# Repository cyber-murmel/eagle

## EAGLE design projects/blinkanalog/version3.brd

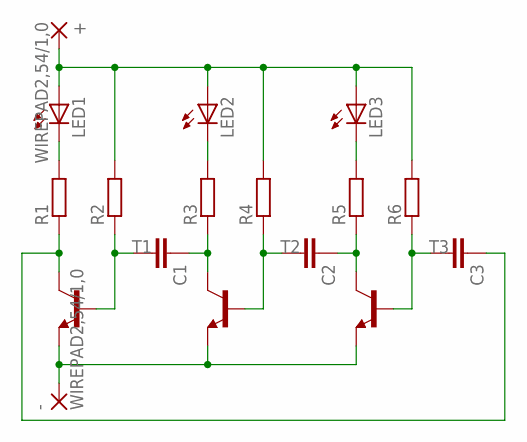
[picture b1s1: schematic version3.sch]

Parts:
+: WIREPAD2,54/1,0; 2,54/1,0
-: WIREPAD2,54/1,0; 2,54/1,0
C1, C2, C3: C-EUC0603; C0603
LED1, LED2, LED3: LEDSML0603; SML0603
R1, R2, R3, R4, R5, R6: R-EU_R0603; R0603
T1, T2, T3: MMBT2222ALT1-NPN-SOT23-BEC; SOT23-BEC

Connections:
unnamed: LED1.C, R1.2
unnamed: C3.1, R1.1, T1.C
unnamed: C1.1, R3.1, T2.C
unnamed: LED2.C, R3.2
unnamed: C2.2, R4.1, T2.B
unnamed: C1.2, R2.1, T1.B
unnamed: +.1, LED1.A, LED2.A, LED3.A, R2.2, R4.2, R6.2
unnamed: C2.1, R5.1, T3.C
unnamed: -.1, T1.E, T2.E, T3.E
unnamed: LED3.C, R5.2
unnamed: C3.2, R6.1, T3.B

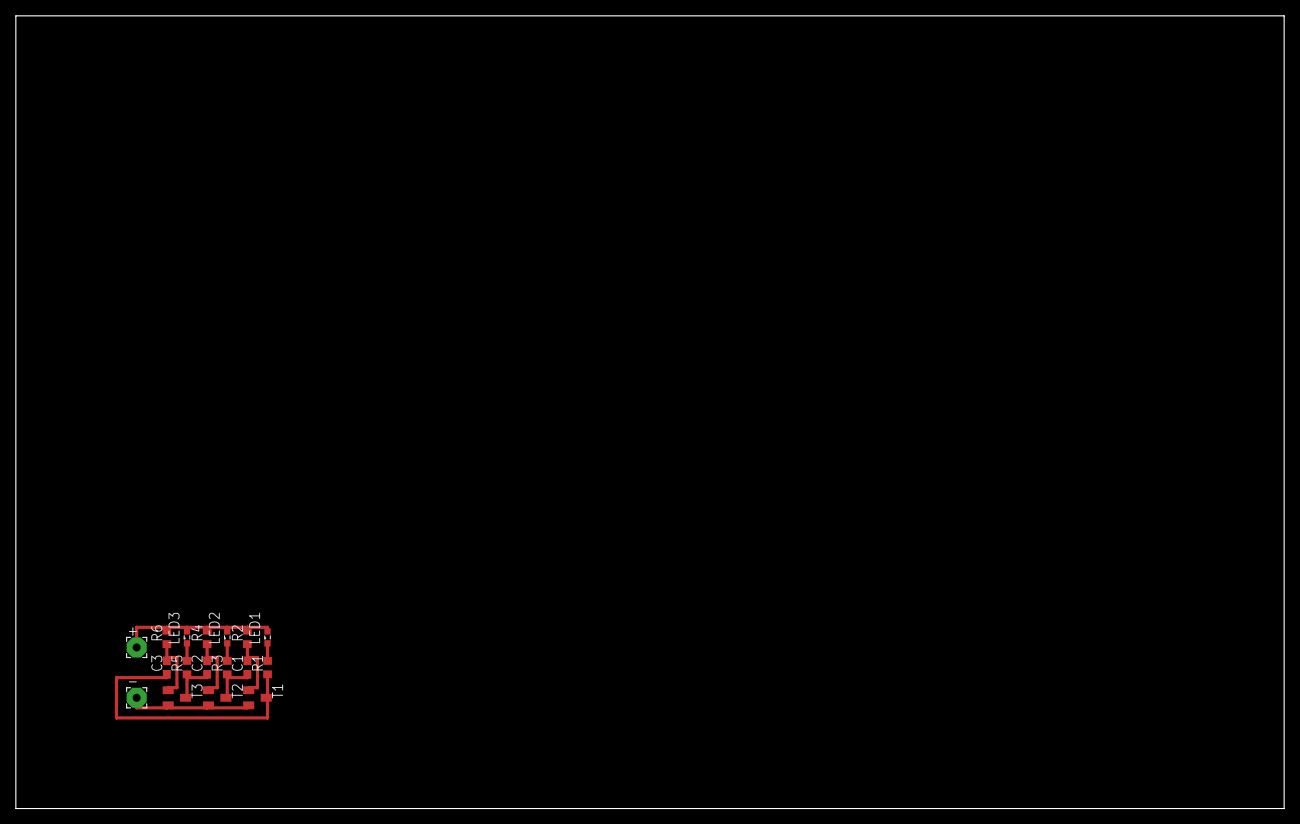
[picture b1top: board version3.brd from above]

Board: 2 copper layers, 160.0 x 100.0 mm, 17 parts (0 on the bottom side), 11 nets.
